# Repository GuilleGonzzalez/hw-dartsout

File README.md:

# Dartsout

## Description

Dartsout is a pcb designed to replace the control board of commercial dartboards to make them compatible with Dartsout, a darts playing application hosted on a server.

Firmware used in the microcontroller of this device is [dartsout](https://github.com/GuilleGonzzalez/fw-dartsout), writed in C. Is in charge of reading the value pressed by the dart and sending it via WiFi to the Dartsout server.

## Microprocessor

Espressif [ESP32-S2-SOLO](https://www.espressif.com/en/products/modules) module (NRND).

## Connectors

The device has 10-pin connectors with a pitch of 2.54, compatible with the connectors of commercial targets. For the connection, it will be necessary to unsolder the connectors of the target to be modified and solder them on this PCB.

They have been duplicated to be flexible with the target connectors to be modified, as sometimes they are in parallel and sometimes they are on top of each other.

In all cases, pin 1 is the one on the right.

## Pin assignment

| PIN     | Func       |
| ------- | ---------- |
| GPIO1   | ROW01      |
| GPIO9   | ROW02      |
| GPIO3   | ROW03      |
| GPIO8   | ROW04      |
| GPIO18  | ROW05      |
| GPIO17  | ROW06      |
| GPIO7   | ROW07      |
| GPIO6   | ROW08      |
| GPIO5   | ROW09      |
| GPIO4   | ROW10      |
| GPIO37  | COL01      |
| GPIO36  | COL02      |
| GPIO35  | COL03      |
| GPIO34  | COL04      |
| GPIO33  | COL05      |
| GPIO21  | COL06      |
| GPIO14  | COL07      |
| GPIO13  | COL08      |
| GPIO12  | COL09      |
| GPIO11  | COL10      |
| GPIO11  | COL10      |
| GPIO1   | USER LED 1 |
| GPIO2   | USER LED 2 |

## LEDs

This PCB has 3 LEDs:

- One power LED, indicating that the device is on.
- Two for user control.

# Changelog

All notable changes to this project will be documented in this section.

The format is based on [Keep a Changelog](https://keepachangelog.com/en/1.0.0/)

## [v0.1.0] - 2024-04-26
### Add
First Dartsout version.

## [unreleased] - 2024-04-24

[unreleased]: https://github.com/GuilleGonzzalez/hw-dartsout

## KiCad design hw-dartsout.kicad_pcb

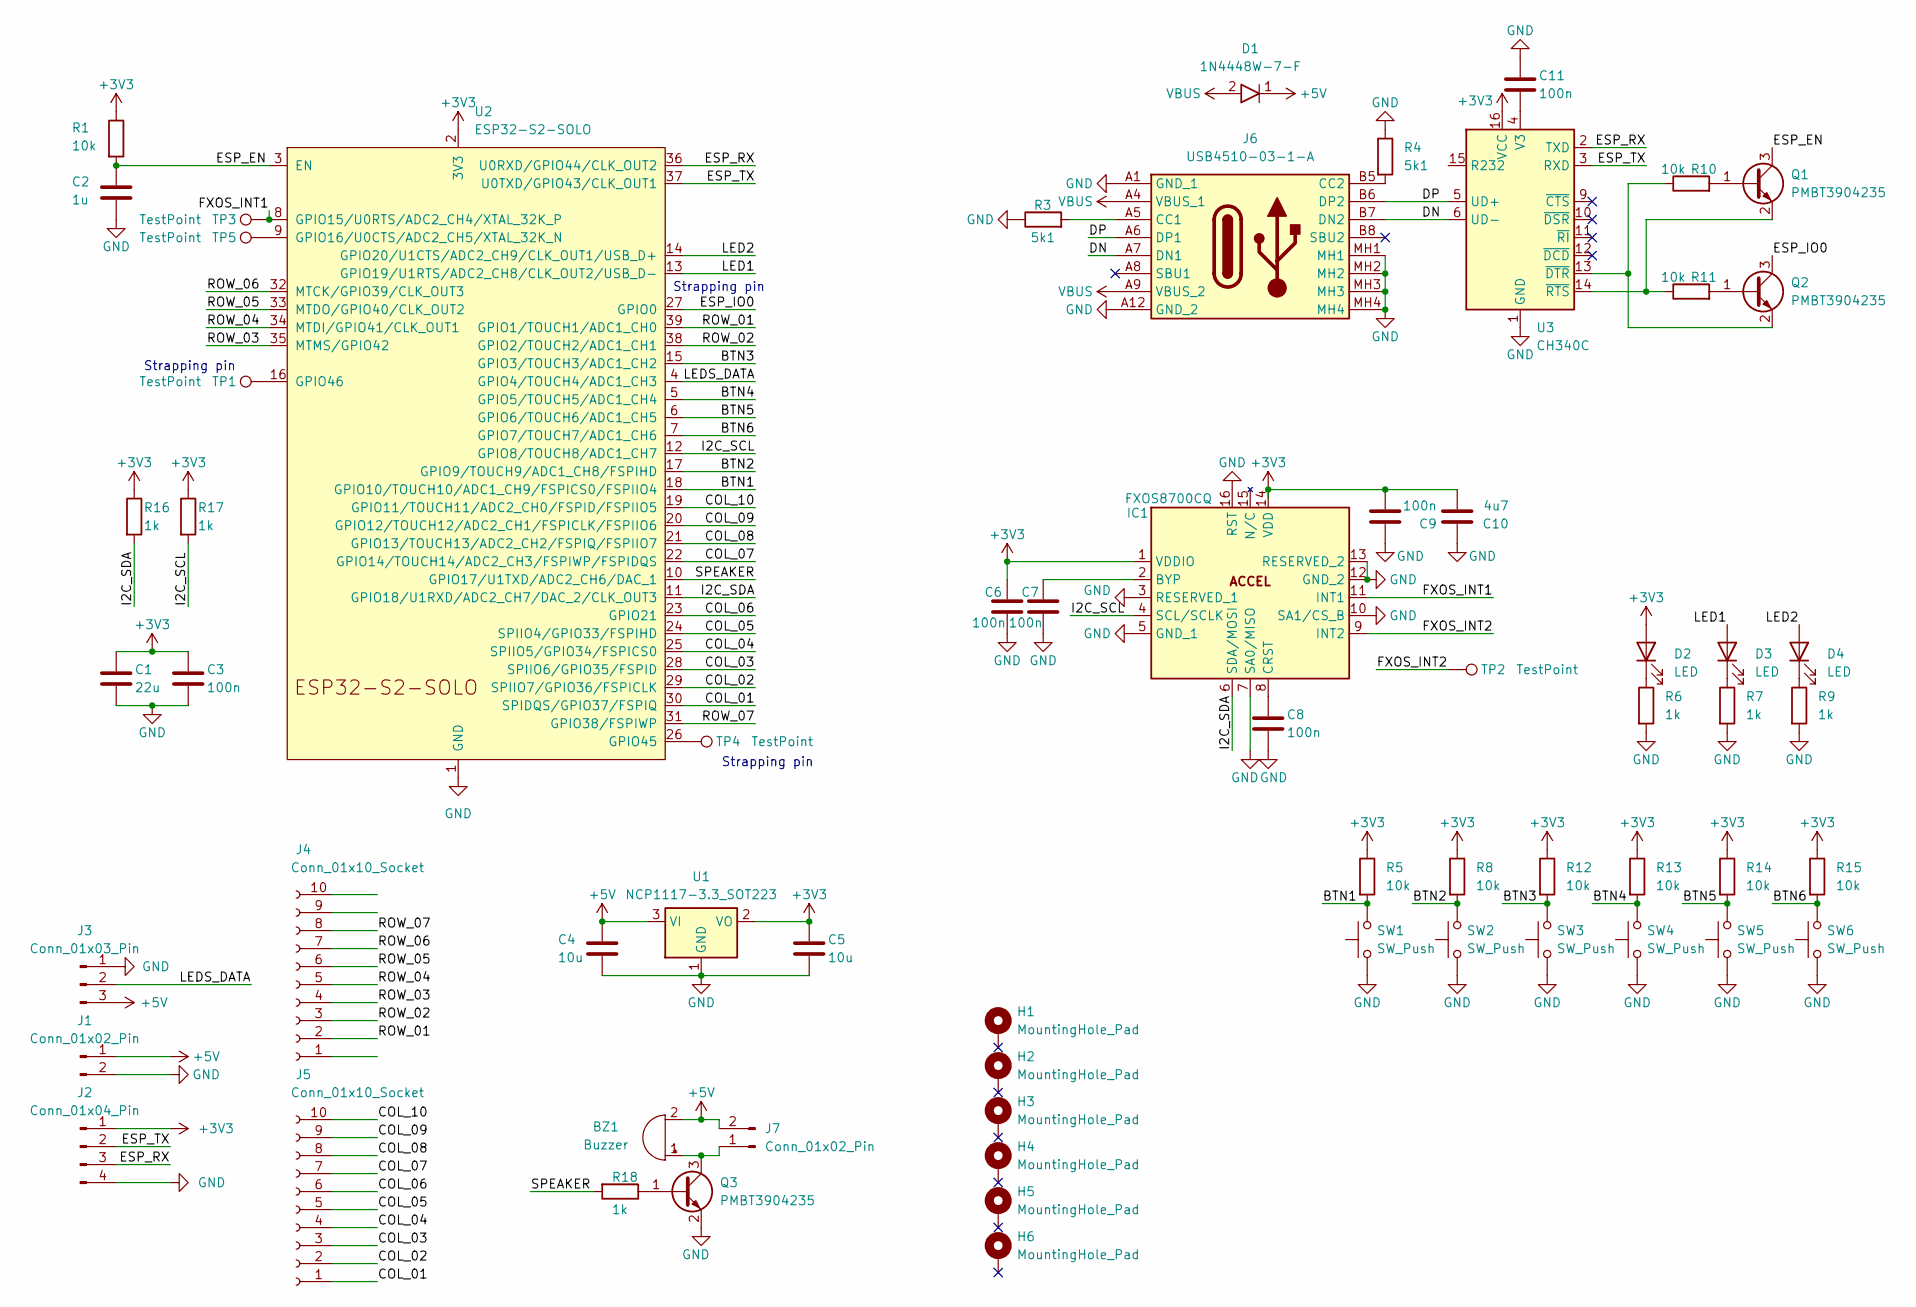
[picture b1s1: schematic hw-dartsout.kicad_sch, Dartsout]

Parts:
BZ1: Buzzer; Buzzer_12x9.5RM7.6
C1: 22u; C_0805_2012Metric
C2: 1u; C_0603_1608Metric
C3, C6, C7, C8, C9, C11: 100n; C_0603_1608Metric
C4, C5: 10u; C_0805_2012Metric
C10: 4u7; C_0805_2012Metric
D1: 1N4448W-7-F; D_SOD-123; Manufacturer_Part_Number 1N4448W-7-F; Mouser Part Number 621-1N4448W-F
D2, D3, D4: LED; LED_0603_1608Metric
H1, H2, H3, H4, H5, H6: MountingHole_Pad; MountingHole_3.2mm_M3_DIN965_Pad_TopBottom
IC1: FXOS8700CQ; Manufacturer_Part_Number FXOS8700CQ; Mouser Part Number N/A
J1: Conn_01x02_Pin; PinHeader_1x02_P2.54mm_Vertical
J2: Conn_01x04_Pin; PinHeader_1x04_P2.54mm_Vertical
J3: Conn_01x03_Pin; JST_XH_B3B-XH-A_1x03_P2.50mm_Vertical
J4, J5: Conn_01x10_Socket; PinSocket_1x10_P2.54mm_Vertical
J6: USB4510-03-1-A; USB4510031A; Mouser Part Number 640-USB4510031A
J7: Conn_01x02_Pin; PinHeader_1x02_P2.54mm_Horizontal
Q1, Q2, Q3: PMBT3904235; SOT-23; Manufacturer_PN PMBT3904,235
R1, R5, R8, R10, R11, R12, R13, R14, R15: 10k; R_0603_1608Metric
R3, R4: 5k1; R_0603_1608Metric
R6, R7, R9, R16, R17, R18: 1k; R_0603_1608Metric
SW1, SW2, SW3, SW4, SW5, SW6: SW_Push; SW_SPST_PTS810
TP1, TP2, TP3, TP4, TP5: TestPoint; TestPoint_Pad_D1.5mm
U1: NCP1117-3.3_SOT223; SOT-223-3_TabPin2
U2: ESP32-S2-SOLO
U3: CH340C; SOIC-16_3.9x9.9mm_P1.27mm

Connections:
+3V3: C1.1, C3.1, C5.1, C6.1, C9.2, C10.2, D2.2 (A), IC1.1 (VDDIO), IC1.14 (VDD), J2.1, R1.1, R5.1, R8.1, R12.1, R13.1, R14.1, R15.1, R16.1, R17.1, U1.2 (VO), U2.2 (3V3), U3.16 (VCC)
+5V: BZ1.2 (-), C4.1, D1.1, J1.1, J3.3, J7.2, U1.3 (VI)
/BTN1: R5.2, SW1.2, U2.18 (GPIO10/TOUCH10/ADC1_CH9/FSPICS0/FSPIIO4)
/BTN2: R8.2, SW2.2, U2.17 (GPIO9/TOUCH9/ADC1_CH8/FSPIHD)
/BTN3: R12.2, SW3.2, U2.15 (GPIO3/TOUCH3/ADC1_CH2)
/BTN4: R13.2, SW4.2, U2.5 (GPIO5/TOUCH5/ADC1_CH4)
/BTN5: R14.2, SW5.2, U2.6 (GPIO6/TOUCH6/ADC1_CH5)
/BTN6: R15.2, SW6.2, U2.7 (GPIO7/TOUCH7/ADC1_CH6)
/COL_01: J5.1, U2.30 (SPIDQS/GPIO37/FSPIQ)
/COL_02: J5.2, U2.29 (SPIIO7/GPIO36/FSPICLK)
/COL_03: J5.3, U2.28 (SPIIO6/GPIO35/FSPID)
/COL_04: J5.4, U2.25 (SPIIO5/GPIO34/FSPICS0)
/COL_05: J5.5, U2.24 (SPIIO4/GPIO33/FSPIHD)
/COL_06: J5.6, U2.23 (GPIO21)
/COL_07: J5.7, U2.22 (GPIO14/TOUCH14/ADC2_CH3/FSPIWP/FSPIDQS)
/COL_08: J5.8, U2.21 (GPIO13/TOUCH13/ADC2_CH2/FSPIQ/FSPIIO7)
/COL_09: J5.9, U2.20 (GPIO12/TOUCH12/ADC2_CH1/FSPICLK/FSPIIO6)
/COL_10: J5.10, U2.19 (GPIO11/TOUCH11/ADC2_CH0/FSPID/FSPIIO5)
/DN: J6.A7 (DN1), J6.B7 (DN2), U3.6 (UD-)
/DP: J6.A6 (DP1), J6.B6 (DP2), U3.5 (UD+)
/ESP_EN: C2.1, Q1.3, R1.2, U2.3 (EN)
/ESP_IO0: Q2.3, U2.27 (GPIO0)
/ESP_RX: J2.3, U2.36 (U0RXD/GPIO44/CLK_OUT2), U3.2 (TXD)
/ESP_TX: J2.2, U2.37 (U0TXD/GPIO43/CLK_OUT1), U3.3 (RXD)
/FXOS_INT1: IC1.11 (INT1), TP3.1, U2.8 (GPIO15/U0RTS/ADC2_CH4/XTAL_32K_P)
/FXOS_INT2: IC1.9 (INT2), TP2.1
/I2C_SCL: IC1.4 (SCL/SCLK), R17.2, U2.12 (GPIO8/TOUCH8/ADC1_CH7)
/I2C_SDA: IC1.6 (SDA/MOSI), R16.2, U2.11 (GPIO18/U1RXD/ADC2_CH7/DAC_2/CLK_OUT3)
/LED1: D3.2 (A), U2.13 (GPIO19/U1RTS/ADC2_CH8/CLK_OUT2/USB_D-)
/LED2: D4.2 (A), U2.14 (GPIO20/U1CTS/ADC2_CH9/CLK_OUT1/USB_D+)
/LEDS_DATA: J3.2, U2.4 (GPIO4/TOUCH4/ADC1_CH3)
/ROW_01: J4.2, U2.39 (GPIO1/TOUCH1/ADC1_CH0)
/ROW_02: J4.3, U2.38 (GPIO2/TOUCH2/ADC1_CH1)
/ROW_03: J4.4, U2.35 (MTMS/GPIO42)
/ROW_04: J4.5, U2.34 (MTDI/GPIO41/CLK_OUT1)
/ROW_05: J4.6, U2.33 (MTDO/GPIO40/CLK_OUT2)
/ROW_06: J4.7, U2.32 (MTCK/GPIO39/CLK_OUT3)
/ROW_07: J4.8, U2.31 (GPIO38/FSPIWP)
/SPEAKER: R18.2, U2.10 (GPIO17/U1TXD/ADC2_CH6/DAC_1)
GND: C1.2, C2.2, C3.2, C4.2, C5.2, C6.2, C7.1, C8.2, C9.1, C10.1, C11.1, IC1.3 (RESERVED_1), IC1.5 (GND_1), IC1.7 (SA0/MISO), IC1.10 (SA1/CS_B), IC1.12 (GND_2), IC1.13 (RESERVED_2), IC1.16 (RST), J1.2, J2.4, J3.1, J6.A1 (GND_1), J6.A12 (GND_2), J6.MH1, J6.MH2, J6.MH3, J6.MH4, Q3.2, R3.1, R4.1, R6.2, R7.2, R9.2, SW1.1, SW2.1, SW3.1, SW4.1, SW5.1, SW6.1, U1.1 (GND), U2.1 (GND), U2.40 (GND), U2.41 (GND), U3.1 (GND)
unnamed: BZ1.1 (+), J7.1, Q3.3
unnamed: D2.1 (K), R6.1
unnamed: D3.1 (K), R7.1
unnamed: D4.1 (K), R9.1
unnamed: C7.2, IC1.2 (BYP)
unnamed: C8.1, IC1.8 (CRST)
unnamed: J6.A5 (CC1), R3.2
unnamed: J6.B5 (CC2), R4.2
unnamed: Q1.1, R10.2
unnamed: Q2.1, R11.2
unnamed: Q3.1, R18.1
unnamed: TP5.1, U2.9 (GPIO16/U0CTS/ADC2_CH5/XTAL_32K_N)
unnamed: TP4.1, U2.26 (GPIO45)
unnamed: TP1.1, U2.16 (GPIO46)
unnamed: C11.2, U3.4 (V3)
unnamed: Q2.2, R10.1, U3.13 (~DTR)
unnamed: Q1.2, R11.1, U3.14 (~RTS)
VBUS: D1.2, J6.A4 (VBUS_1), J6.A9 (VBUS_2)

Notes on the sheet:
Strapping pin

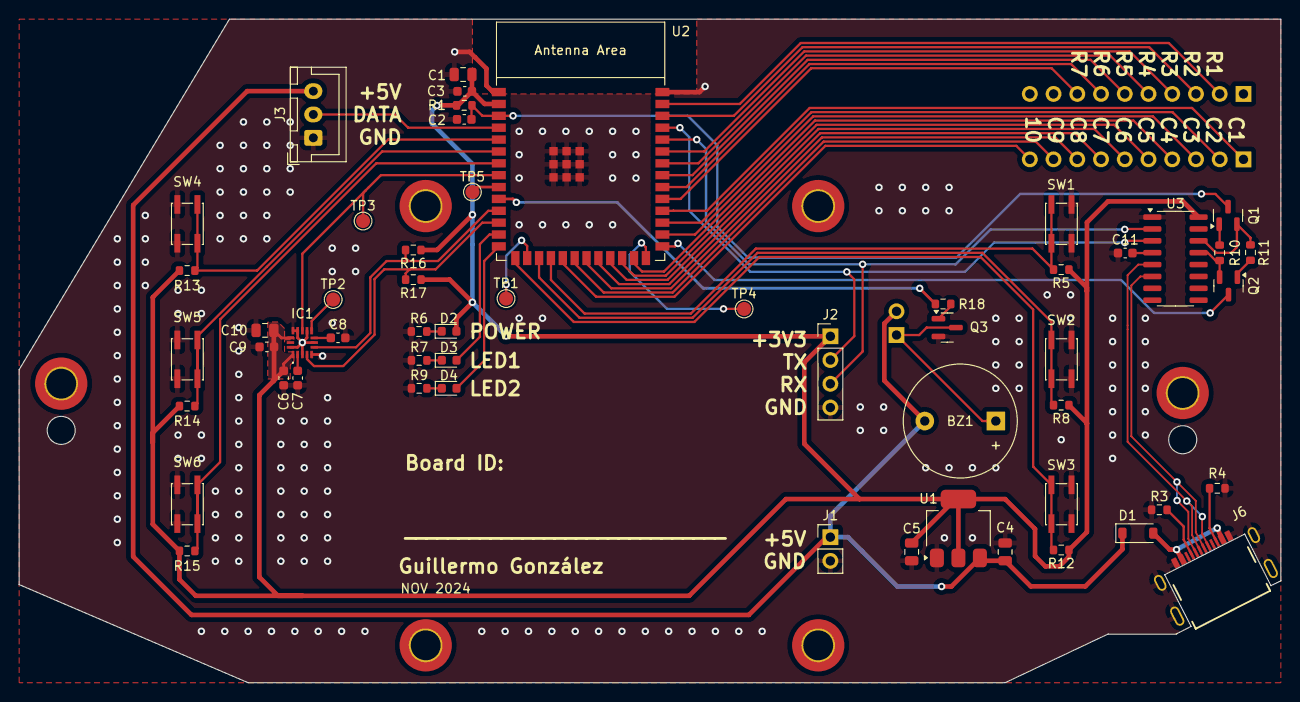
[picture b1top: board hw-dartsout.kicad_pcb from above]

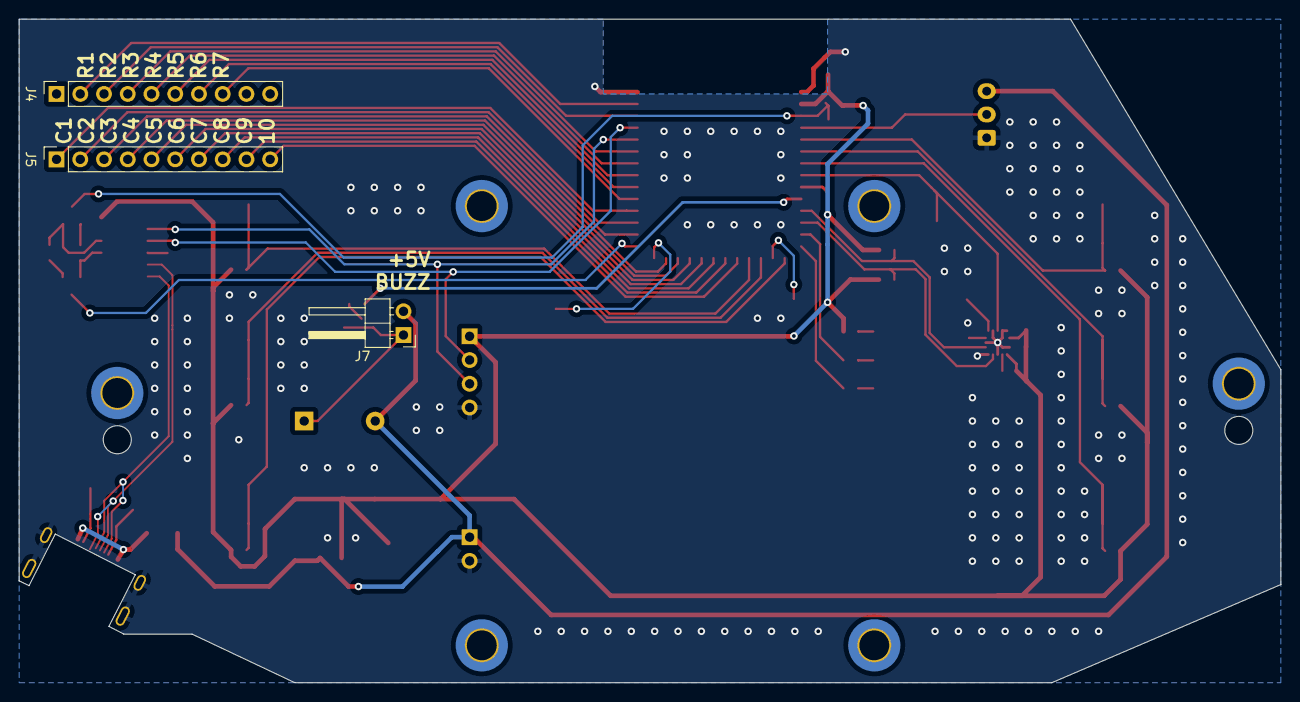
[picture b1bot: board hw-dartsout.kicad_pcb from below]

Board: 2 copper layers, 135.0 x 71.0 mm, 64 parts (3 on the bottom side), 58 nets.

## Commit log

2024-04-24 Start SCH
2024-04-24 First draft placement and layout
2024-04-25 PCB routed
2024-04-26 Finish route, serigrphy and checks
2024-04-26 Revision 0.1
2024-11-06 Changed sch and start with layout for next version
2024-11-16 Add changes for revision 0.2
